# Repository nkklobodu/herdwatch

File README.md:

View this project on [CADLAB.io](https://cadlab.io/project/28751). 

# herdwatch

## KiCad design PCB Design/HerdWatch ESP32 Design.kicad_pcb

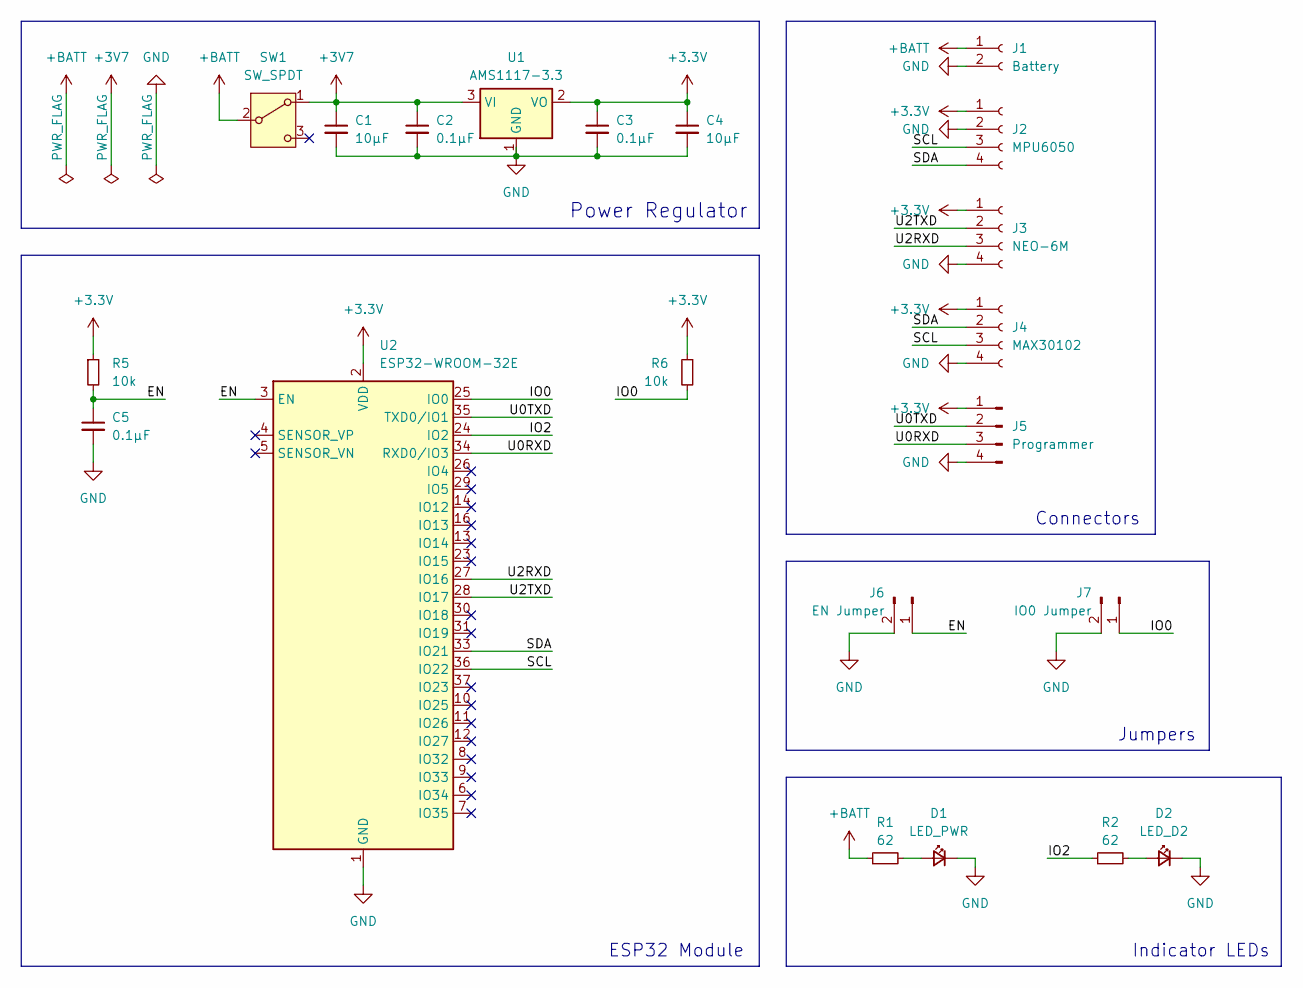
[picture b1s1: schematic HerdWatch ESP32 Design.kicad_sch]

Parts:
C1, C4: 10µF; C_1206_3216Metric_Pad1.33x1.80mm_HandSolder
C2, C3, C5: 0.1µF; C_1206_3216Metric_Pad1.33x1.80mm_HandSolder
D1: LED_PWR; LED_D5.0mm_Horizontal_O1.27mm_Z3.0mm
D2: LED_D2; LED_1206_3216Metric_Pad1.42x1.75mm_HandSolder
J1: Battery; JST_XH_B2B-XH-A_1x02_P2.50mm_Vertical
J2: MPU6050; JST_XH_B4B-XH-A_1x04_P2.50mm_Vertical
J3: NEO-6M; JST_XH_B4B-XH-A_1x04_P2.50mm_Vertical
J4: MAX30102; JST_XH_B4B-XH-A_1x04_P2.50mm_Vertical
J5: Programmer; PinHeader_1x04_P2.54mm_Vertical
J6: EN Jumper; PinHeader_1x02_P2.54mm_Vertical
J7: IO0 Jumper; PinHeader_1x02_P2.54mm_Vertical
R1, R2: 62; R_1206_3216Metric_Pad1.30x1.75mm_HandSolder
R5, R6: 10k; R_1206_3216Metric_Pad1.30x1.75mm_HandSolder
SW1: SW_SPDT; SW_Slide_SPDT_Angled_CK_OS102011MA1Q
U1: AMS1117-3.3; SOT-223-3_TabPin2
U2: ESP32-WROOM-32E; ESP32-WROOM-32D

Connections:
+3.3V: C3.1, C4.1, J2.1, J3.1, J4.1, J5.1, R5.1, R6.1, U1.2 (VO), U2.2 (VDD); also elsewhere on the board
+3V7: C1.1, C2.1, SW1.1 (A), U1.3 (VI)
+BATT: J1.1, R1.1, SW1.2 (B)
/EN: C5.1, J6.1, R5.2, U2.3 (EN); also elsewhere on the board
/IO0: J7.1, R6.2, U2.25 (IO0)
/IO2: R2.1, U2.24 (IO2)
/SCL: J2.3, J4.3, U2.36 (IO22)
/SDA: J2.4, J4.2, U2.33 (IO21)
/U0RXD: J5.3, U2.34 (RXD0/IO3)
/U0TXD: J5.2, U2.35 (TXD0/IO1)
/U2RXD: J3.3, U2.27 (IO16)
/U2TXD: J3.2, U2.28 (IO17)
GND: C1.2, C2.2, C3.2, C4.2, C5.2, D1.1 (K), D2.1 (K), J1.2, J2.2, J3.4, J4.4, J5.4, J6.2, J7.2, U1.1 (GND), U2.1 (GND), U2.15 (GND), U2.38 (GND), U2.39 (GND)
unnamed: D1.2 (A), R1.2
unnamed: D2.2 (A), R2.2

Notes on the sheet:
Indicator LEDs
Power Regulator
Jumpers
Connectors
ESP32 Module

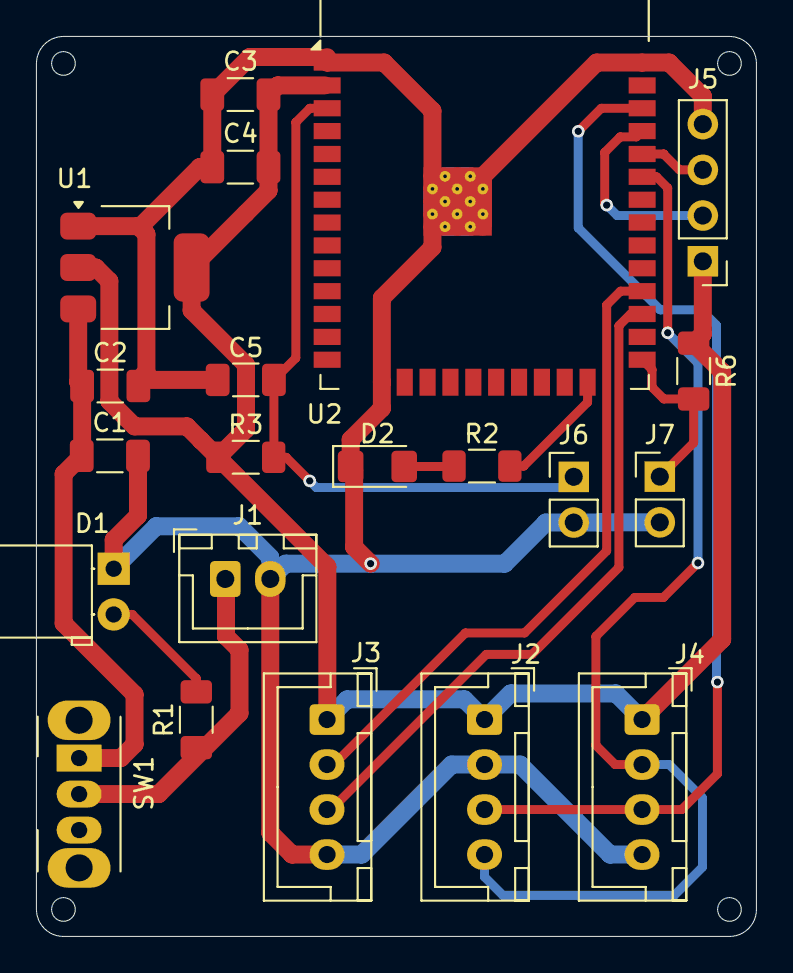
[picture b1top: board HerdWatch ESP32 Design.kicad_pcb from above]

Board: 2 copper layers, 40.0 x 50.0 mm, 21 parts (0 on the bottom side), 15 nets.

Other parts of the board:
R3: 10k; R_1206_3216Metric_Pad1.30x1.75mm_HandSolder

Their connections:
+3.3V: R3.1; also elsewhere on the board
/EN: R3.2; also elsewhere on the board

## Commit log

2024-12-19 Backlink to CADLAB.io has been added.
2024-12-19 Updated project files
2024-12-19 Updated gitignore
2024-12-19 Removed 'PCB Design/HerdWatch ESP32 Design.kicad_prl'
